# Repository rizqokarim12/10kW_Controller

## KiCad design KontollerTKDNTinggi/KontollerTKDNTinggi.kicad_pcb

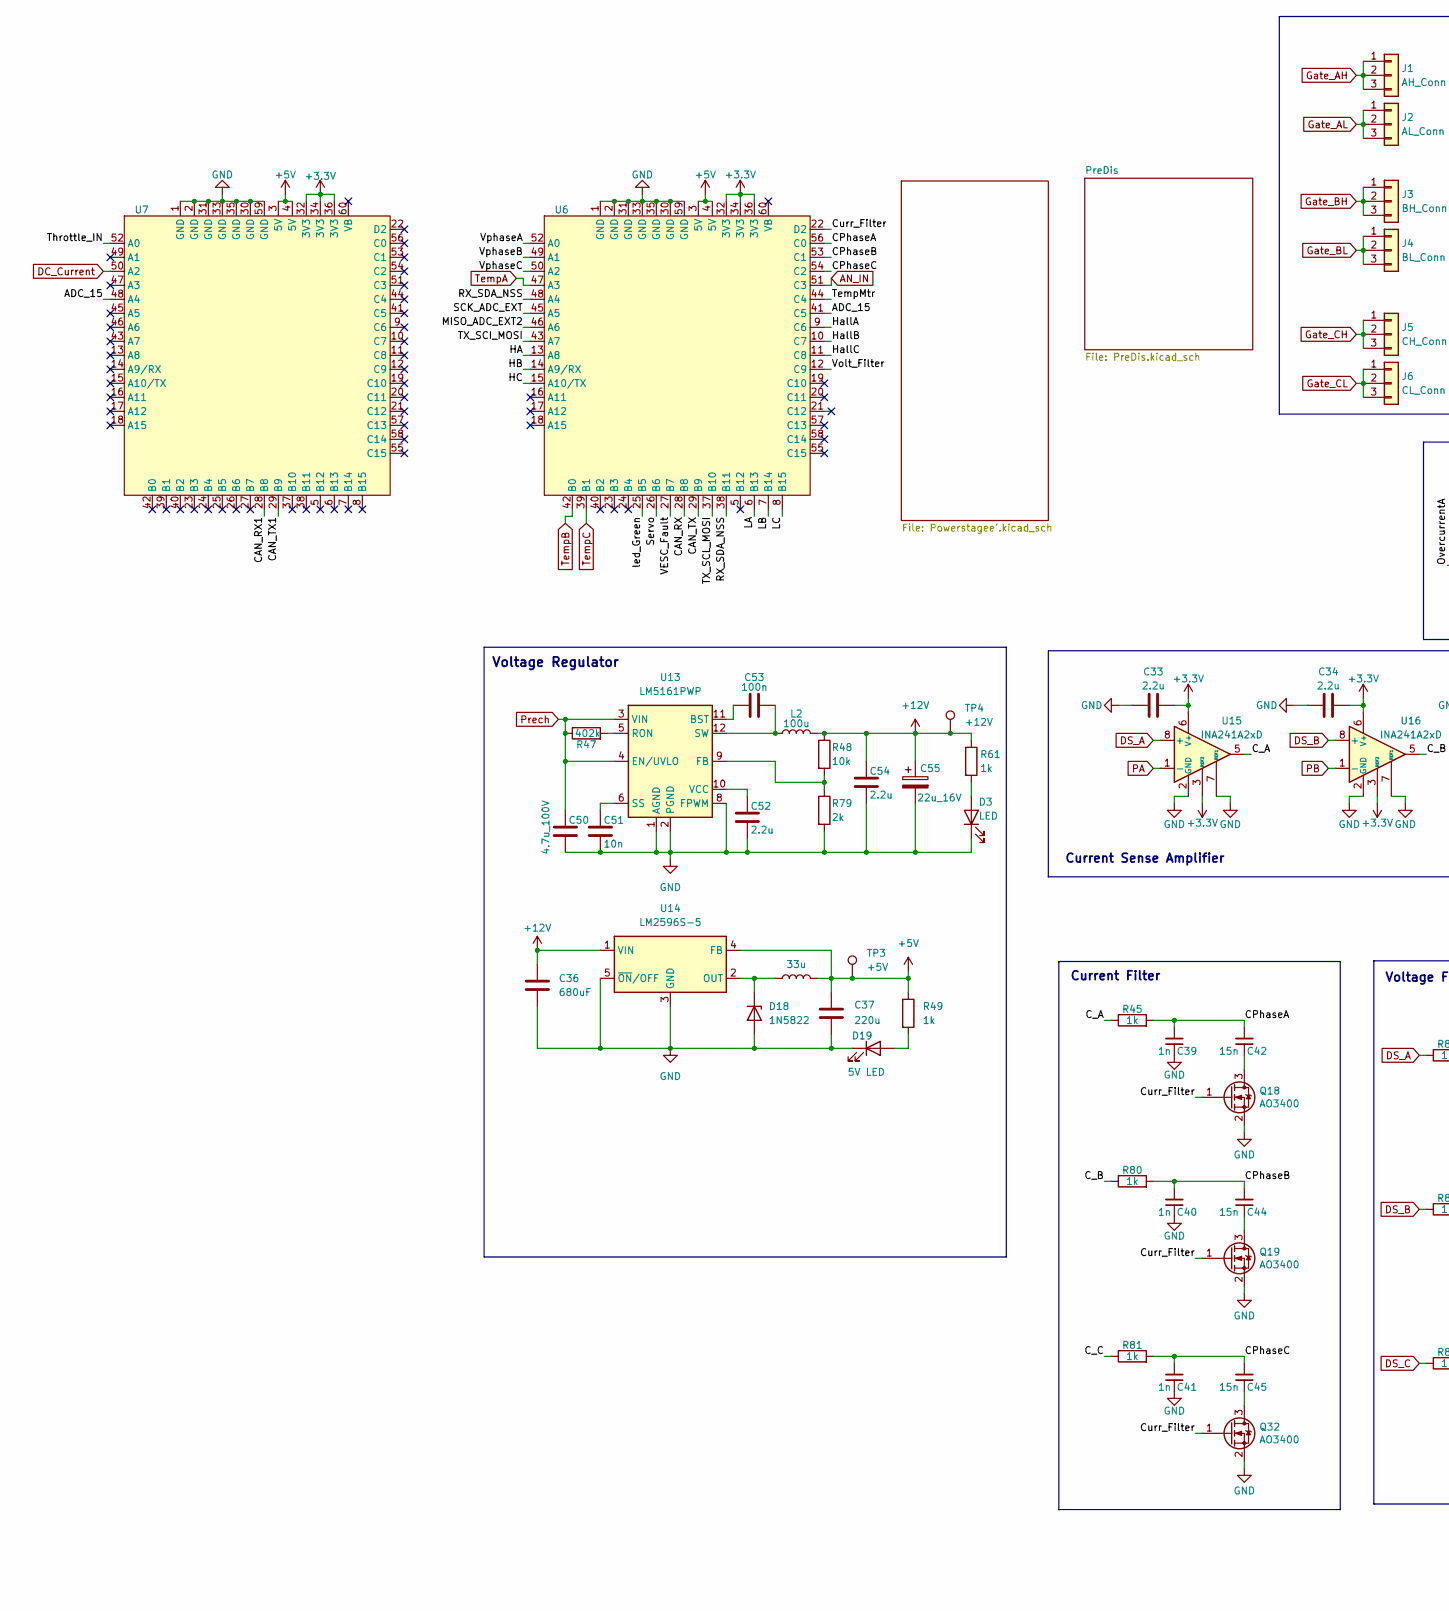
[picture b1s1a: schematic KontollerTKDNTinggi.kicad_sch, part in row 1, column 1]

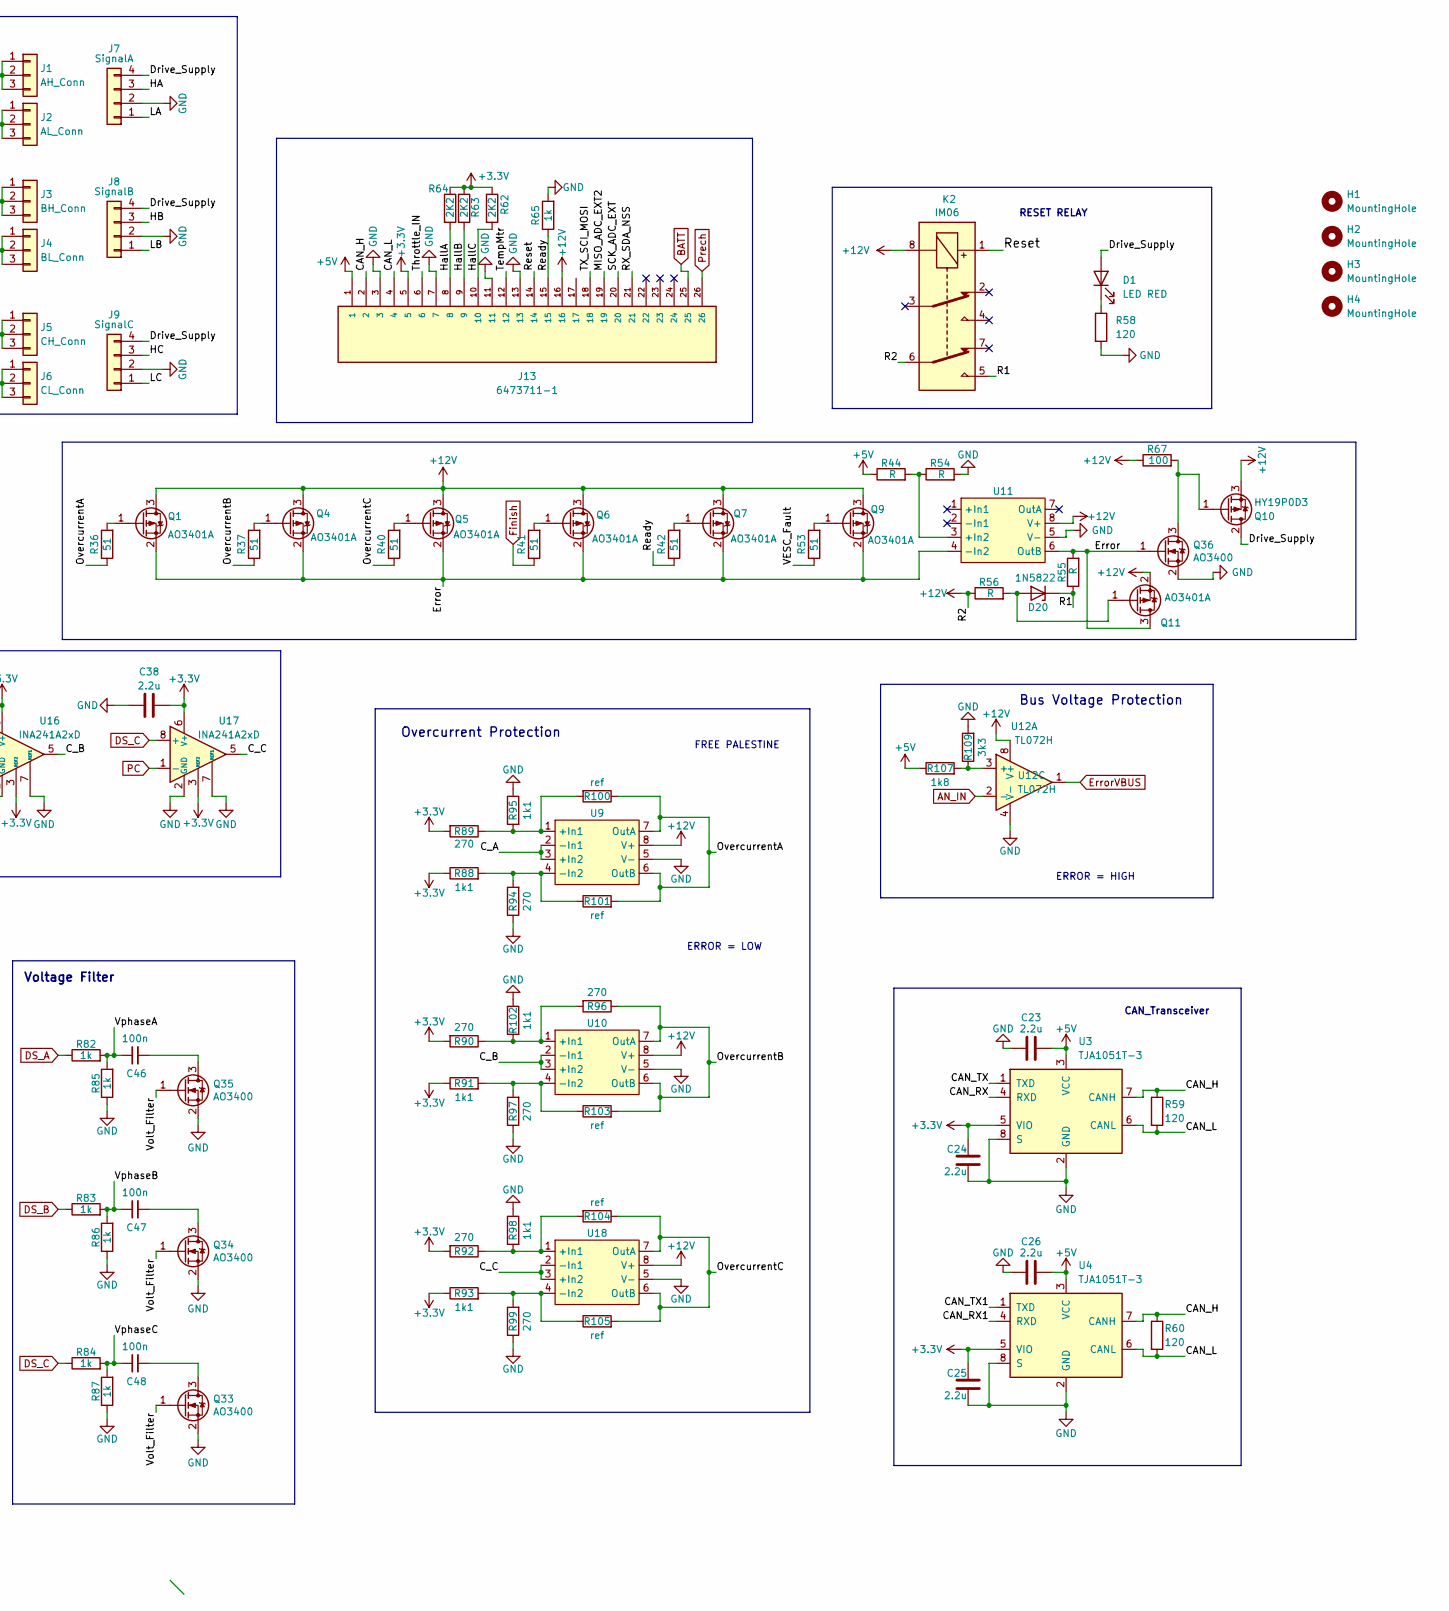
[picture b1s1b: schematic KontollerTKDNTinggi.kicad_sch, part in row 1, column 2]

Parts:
C23, C24, C25, C26, C33, C34, C38, C52, C54: 2.2u; C_0805_2012Metric_Pad1.18x1.45mm_HandSolder
C36: 680uF; CP_Elec_10x10
C37: 220u; C_Elec_6.3x5.4
C39, C40, C41: 1n; C_0805_2012Metric_Pad1.18x1.45mm_HandSolder
C42, C44, C45: 15n; C_0805_2012Metric_Pad1.18x1.45mm_HandSolder
C46, C47, C48, C53: 100n; C_0805_2012Metric_Pad1.18x1.45mm_HandSolder
C50: 4.7u_100V; CP_Elec_6.3x5.2
C51: 10n; C_0805_2012Metric_Pad1.18x1.45mm_HandSolder
C55: 22u_16V; CP_Elec_5x5.4
D1: LED RED; LED_0805_2012Metric_Pad1.15x1.40mm_HandSolder
D3: LED; LED_0805_2012Metric_Pad1.15x1.40mm_HandSolder
D18, D20: 1N5822; D_SMA_Handsoldering
D19: 5V LED; LED_0805_2012Metric_Pad1.15x1.40mm_HandSolder
H1, H2, H3, H4: MountingHole; MountingHole_3mm_Pad_Via
J1: AH_Conn; PinSocket_1x03_P2.54mm_Vertical_SMD_Pin1Left
J2: AL_Conn; PinSocket_1x03_P2.54mm_Vertical_SMD_Pin1Left
J3: BH_Conn; PinSocket_1x03_P2.54mm_Vertical_SMD_Pin1Left
J4: BL_Conn; PinSocket_1x03_P2.54mm_Vertical_SMD_Pin1Left
J5: CH_Conn; PinSocket_1x03_P2.54mm_Vertical_SMD_Pin1Left
J6: CL_Conn; PinSocket_1x03_P2.54mm_Vertical_SMD_Pin1Left
J7: SignalA; PinSocket_1x04_P2.54mm_Vertical_SMD_Pin1Left
J8: SignalB; PinSocket_1x04_P2.54mm_Vertical_SMD_Pin1Left
J9: SignalC; PinSocket_1x04_P2.54mm_Vertical_SMD_Pin1Left
J13: 6473711-1; TE_6473711-1; PART_REV A
K2: IM06; IM06D
L2: 100u; INDM1250X1250X600
L5: 33u; L_10.4x10.4_H4.8
Q1, Q4, Q5, Q6, Q7, Q9, Q11: AO3401A; SOT-23_Handsoldering
Q10: HY19P0D3; TO-252-2
Q18, Q19, Q32, Q33, Q34, Q35, Q36: AO3400; SOT-23_Handsoldering
R36, R37, R40, R41, R42, R53: 51; R_0805_2012Metric_Pad1.20x1.40mm_HandSolder
R44, R54, R55, R56: R; R_0805_2012Metric_Pad1.20x1.40mm_HandSolder
R45, R49, R61, R65, R80, R81, R82, R83, R84, R85, R86, R87: 1k; R_0805_2012Metric_Pad1.20x1.40mm_HandSolder
R47: 402k; R_0805_2012Metric_Pad1.20x1.40mm_HandSolder
R48: 10k; R_0805_2012Metric_Pad1.20x1.40mm_HandSolder
R58, R59, R60: 120; R_0805_2012Metric_Pad1.20x1.40mm_HandSolder
R62, R63, R64: 2K2; R_0805_2012Metric_Pad1.20x1.40mm_HandSolder
R67: 100; R_0805_2012Metric_Pad1.20x1.40mm_HandSolder
R79: 2k; R_0805_2012Metric_Pad1.20x1.40mm_HandSolder
R88, R91, R93, R95, R98, R102: 1k1; R_0805_2012Metric_Pad1.20x1.40mm_HandSolder
R89, R90, R92, R94, R96, R97, R99: 270; R_0805_2012Metric_Pad1.20x1.40mm_HandSolder
R100, R101, R103, R104, R105: ref; R_0805_2012Metric_Pad1.20x1.40mm_HandSolder
R107: 1k8; R_0805_2012Metric_Pad1.20x1.40mm_HandSolder
R109: 3k3; R_0805_2012Metric_Pad1.20x1.40mm_HandSolder
TP3: +5V; TestPoint_Pad_2.0x2.0mm
TP4: +12V; TestPoint_Pad_2.0x2.0mm
U3, U4: TJA1051T-3; SOIC-8_3.9x4.9mm_P1.27mm
U6, U7: STM32F405Weact
U9, U10, U11, U18: SOIC-8_3.9x4.9mm_P1.27mm
U12: TL072H; SOIC-8_3.9x4.9mm_P1.27mm
U13: LM5161PWP; HTSSOP-14-1EP_4.4x5mm_P0.65mm_EP3.4x5mm_Mask3x3.1mm
U14: LM2596S-5; TO-263-5_TabPin3
U15, U16, U17: INA241A2xD; SOIC-8_3.9x4.9mm_P1.27mm

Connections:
+12V: C36.1, C54.1, C55.1, J13.16, K2.6, K2.8, L2.2, Q1.3 (D), Q4.3 (D), Q5.3 (D), Q6.3 (D), Q7.3 (D), Q9.3 (D), Q10.3 (S), Q11.2 (S), R48.1, R56.1, R61.1, R67.1, TP4.1, U9.8 (V+), U10.8 (V+), U11.8 (V+), U12.8 (V+), U14.1 (VIN), U18.8 (V+); also elsewhere on the board
/ADC_15: U6.41 (C5), U7.48 (A4)
/CAN_H: J13.2, R59.1, R60.1, U3.7 (CANH), U4.7 (CANH)
/CAN_L: J13.4, R59.2, R60.2, U3.6 (CANL), U4.6 (CANL)
/CAN_RX: U3.4 (RXD), U6.28 (B8)
/CAN_RX1: U4.4 (RXD), U7.28 (B8)
/CAN_TX: U3.1 (TXD), U6.29 (B9)
/CAN_TX1: U4.1 (TXD), U7.29 (B9)
/CPhaseA: C39.2, C42.2, R45.2, U6.56 (C0)
/CPhaseB: C40.2, C44.2, R80.2, U6.53 (C1)
/CPhaseC: C41.2, C45.2, R81.2, U6.54 (C2)
/C_A: R45.1, U9.2 (-In1), U9.3 (+In2), U15.5
/C_B: R80.1, U10.2 (-In1), U10.3 (+In2), U16.5
/C_C: R81.1, U17.5, U18.2 (-In1), U18.3 (+In2)
/Curr_Filter: Q18.1 (G), Q19.1 (G), Q32.1 (G), U6.22 (D2)
/Drive_Supply: D1.2 (A), J7.4, J8.4, J9.4, Q10.2 (D)
/HA: J7.3, U6.13 (A8)
/HB: J8.3, U6.14 (A9/RX)
/HC: J9.3, U6.15 (A10/TX)
/HallA: J13.8, R64.2, U6.9 (C6)
/HallB: J13.9, R63.2, U6.10 (C7)
/HallC: J13.10, R62.2, U6.11 (C8)
/LA: J7.1, U6.6 (B13)
/LB: J8.1, U6.7 (B14)
/LC: J9.1, U6.8 (B15)
/MISO_ADC_EXT2: J13.19, U6.46 (A6)
/OvercurrentA: R36.1, R100.1, R101.2, U9.6 (OutB), U9.7 (OutA)
/OvercurrentB: R37.1, R96.1, R103.2, U10.6 (OutB), U10.7 (OutA)
/OvercurrentC: R40.1, R104.1, R105.2, U18.6 (OutB), U18.7 (OutA)
/RX_SDA_NSS: J13.21, U6.38 (B11), U6.48 (A4)
/Ready: J13.15, R42.1, R65.1
/Reset: J13.14, K2.1
/SCK_ADC_EXT: J13.20, U6.45 (A5)
/Servo: U6.26 (B6)
/TX_SCI_MOSI: J13.18, U6.43 (A7)
/TX_SCL_MOSI: U6.37 (B10)
/TempMtr: J13.12, U6.44 (C4)
/Throttle_IN: J13.6, U7.52 (A0)
/VESC_Fault: R53.1, U6.27 (B7)
/Volt_Filter: Q33.1 (G), Q34.1 (G), Q35.1 (G), U6.12 (C9)
/VphaseA: C46.1, R82.2, R85.2, U6.52 (A0)
/VphaseB: C47.1, R83.2, R86.2, U6.49 (A1)
/VphaseC: C48.1, R84.2, R87.2, U6.50 (A2)
/led_Green: U6.25 (B5)
AN_IN: U6.51 (C3), U12.2 (-); also elsewhere on the board
DC_Current: U7.50 (A2); also elsewhere on the board
DS_A: R82.1, U15.8 (+); also elsewhere on the board
DS_B: R83.1, U16.8 (+); also elsewhere on the board
DS_C: R84.1, U17.8 (+); also elsewhere on the board
ErrorVBUS: U12.1; also elsewhere on the board
Finish: R41.1; also elsewhere on the board
GND: C23.1, C24.1, C25.1, C26.1, C33.1, C34.1, C36.2, C37.2, C38.1, C39.1, C40.1, C41.1, C50.2, C51.2, C52.2, C54.2, C55.2, D3.1 (K), D18.2 (A), D19.1 (K), J7.2, J8.2, J9.2, J13.3, J13.7, J13.11, J13.13, Q18.2 (S), Q19.2 (S), Q32.2 (S), Q33.2 (S), Q34.2 (S), Q35.2 (S), Q36.2 (S), R54.2, R58.2, R65.2, R79.2, R85.1, R86.1, R87.1, R94.1, R95.1, R97.1, R98.1, R99.1, R102.1, R109.2, U3.2 (GND), U3.8 (S), U4.2 (GND), U4.8 (S), U6.1 (GND), U6.2 (GND), U6.30 (GND), U6.31 (GND), U6.33 (GND), U6.35 (GND), U6.59 (GND), U7.1 (GND), U7.2 (GND), U7.30 (GND), U7.31 (GND), U7.33 (GND), U7.35 (GND), U7.59 (GND), U9.5 (V-), U10.5 (V-), U11.5 (V-), U12.4 (V-), U13.1 (AGND), U13.2 (PGND), U13.8 (FPWM), U13.15 (AGND), U14.3 (GND), U14.5 (~ON/OFF), U15.2 (GND), U15.4 (GND), U15.7 (REF1), U16.2 (GND), U16.4 (GND), U16.7 (REF1), U17.2 (GND), U17.4 (GND), U17.7 (REF1), U18.5 (V-); also elsewhere on the board
Gate_AH: J1.1, J1.2, J1.3; also elsewhere on the board
Gate_AL: J2.1, J2.2, J2.3; also elsewhere on the board
Gate_BH: J3.1, J3.2, J3.3; also elsewhere on the board
Gate_BL: J4.1, J4.2, J4.3; also elsewhere on the board
Gate_CH: J5.1, J5.2, J5.3; also elsewhere on the board
Gate_CL: J6.1, J6.2, J6.3; also elsewhere on the board
unnamed: C53.1, L2.1, U13.12 (SW), U13.13 (SW)
unnamed: D1.1 (K), R58.1
unnamed: D3.2 (A), R61.2
unnamed: D18.1 (K), L5.1, U14.2 (OUT)
unnamed: D19.2 (A), R49.2
unnamed: D20.2 (A), Q11.1 (G), R56.2
unnamed: Q1.1 (G), R36.2
unnamed: Q4.1 (G), R37.2
unnamed: Q5.1 (G), R40.2
unnamed: Q6.1 (G), R41.2
unnamed: Q7.1 (G), R42.2
unnamed: Q9.1 (G), R53.2
unnamed: C42.1, Q18.3 (D)
unnamed: C44.1, Q19.3 (D)
unnamed: C45.1, Q32.3 (D)
unnamed: C48.2, Q33.3 (D)
unnamed: C47.2, Q34.3 (D)
unnamed: C46.2, Q35.3 (D)
unnamed: R89.1, R95.2, R100.2, U9.1 (+In1)
unnamed: R88.2, R94.2, R101.1, U9.4 (-In2)
unnamed: R90.1, R96.2, R102.2, U10.1 (+In1)
unnamed: R91.2, R97.2, R103.1, U10.4 (-In2)
unnamed: R44.2, R54.1, U11.3 (+In2)
unnamed: R107.2, R109.1, U12.3 (+)
unnamed: C53.2, U13.11 (BST)
unnamed: R48.2, R79.1, U13.9 (FB)
unnamed: R47.2, U13.5 (RON)
unnamed: C51.1, U13.6 (SS)
unnamed: C52.1, U13.10 (VCC)
unnamed: R92.1, R98.2, R104.2, U18.1 (+In1)
unnamed: R93.2, R99.2, R105.1, U18.4 (-In2)
PA: U15.1 (-); also elsewhere on the board
PB: U16.1 (-); also elsewhere on the board
PC: U17.1 (-); also elsewhere on the board
Prech: C50.1, J13.26, R47.1, U13.3 (VIN), U13.4 (EN/UVLO); also elsewhere on the board
TempA: U6.47 (A3); also elsewhere on the board
TempB: U6.42 (B0); also elsewhere on the board
TempC: U6.39 (B1); also elsewhere on the board

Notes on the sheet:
Voltage Regulator
CAN_Transceiver
Overcurrent Protection
RESET RELAY
Current Filter
Current Sense Amplifier
Bus Voltage Protection
Voltage Filter
ERROR = LOW
ERROR = HIGH
FREE PALESTINE

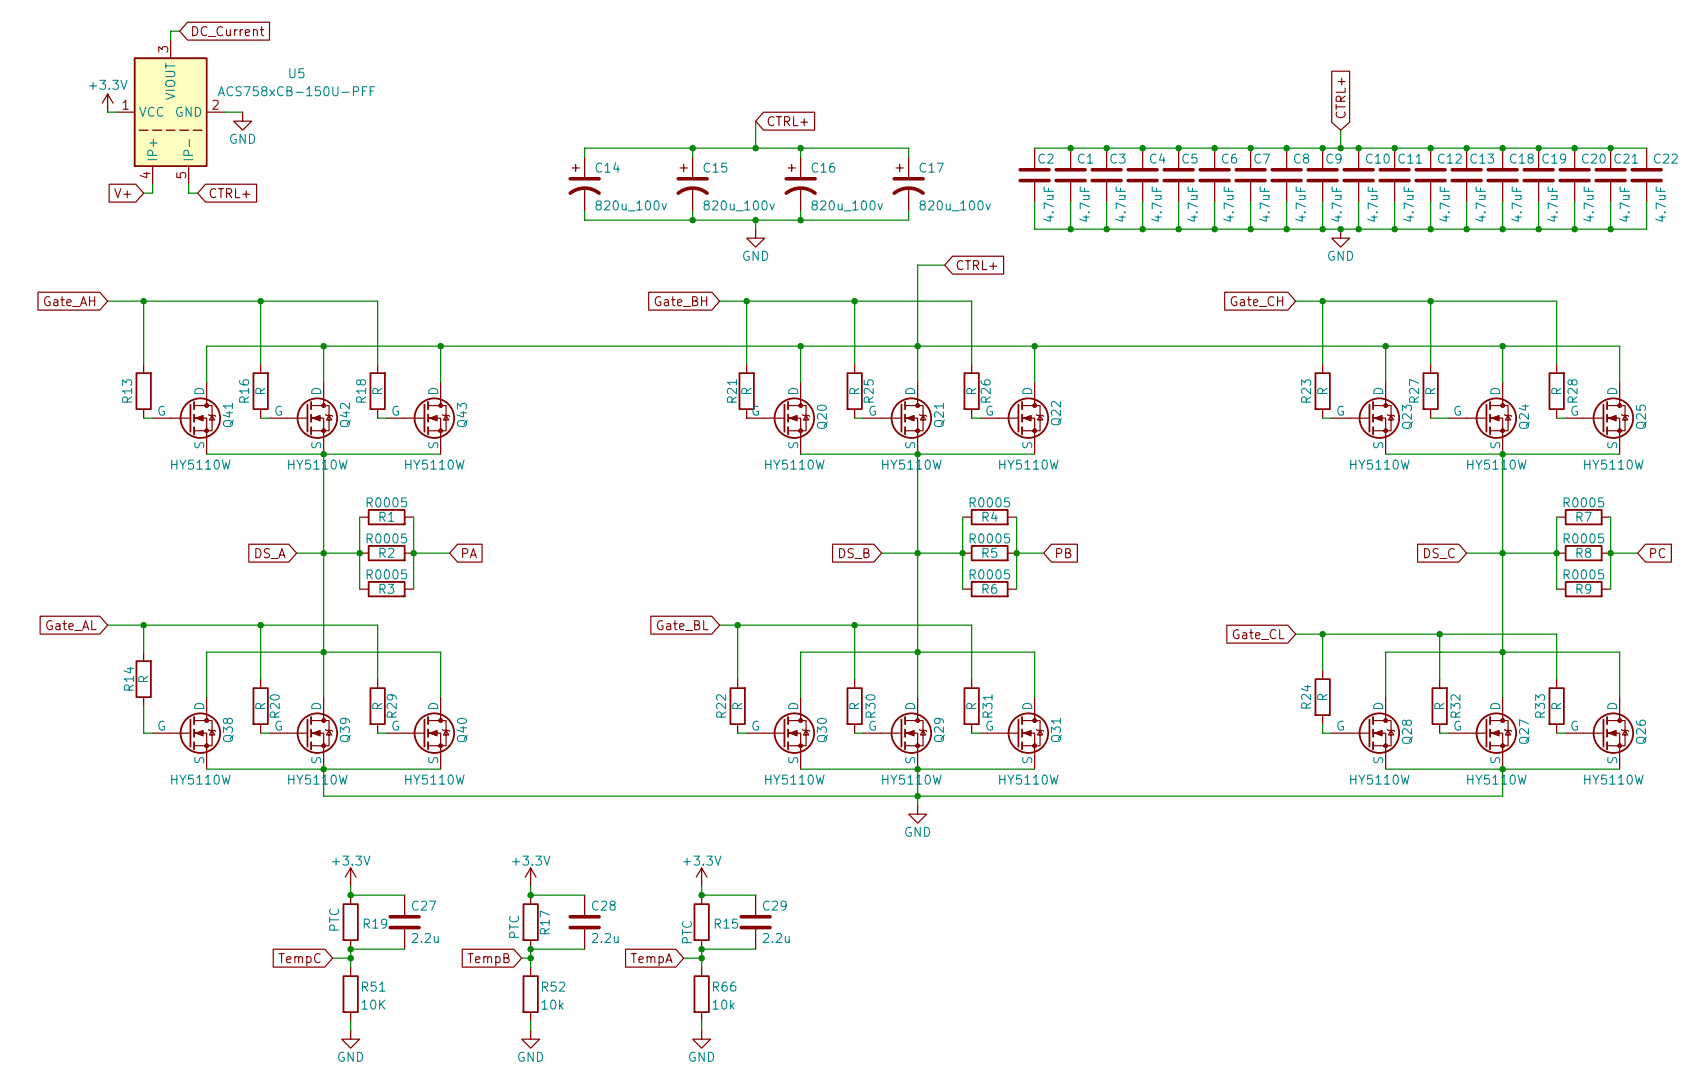
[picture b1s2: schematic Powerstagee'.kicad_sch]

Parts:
C1, C2, C3, C4, C5, C6, C7, C8, C9, C10, C11, C12, C13, C18, C19, C20, C21, C22: 4.7uF; C_1206_3216Metric_Pad1.33x1.80mm_HandSolder
C14, C15, C16, C17: 820u_100v; CP_Radial_D18.0mm_P7.50mm
C27, C28, C29: 2.2u; C_0805_2012Metric_Pad1.18x1.45mm_HandSolder
Q20, Q21, Q22, Q23, Q24, Q25, Q26, Q27, Q28, Q29, Q30, Q31, Q38, Q39, Q40, Q41, Q42, Q43: HY5110W; TO-247 Horizontal Tabup
R1, R2, R3, R4, R5, R6, R7, R8, R9: R0005; R_2512_6332Metric_Pad1.40x3.35mm_HandSolder
R13, R14, R16, R18, R20, R21, R22, R23, R24, R25, R26, R27, R28, R29, R30, R31, R32, R33: R; R_0805_2012Metric_Pad1.20x1.40mm_HandSolder
R15, R17, R19: PTC; R_Axial_DIN0204_L3.6mm_D1.6mm_P1.90mm_Vertical
R51: 10K; R_0805_2012Metric_Pad1.20x1.40mm_HandSolder
R52, R66: 10k; R_0805_2012Metric_Pad1.20x1.40mm_HandSolder
U5: ACS758xCB-150U-PFF; Allegro_CB_PFF

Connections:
CTRL+: C1.1, C2.1, C3.1, C4.1, C5.1, C6.1, C7.1, C8.1, C9.1, C10.1, C11.1, C12.1, C13.1, C14.1, C15.1, C16.1, C17.1, C18.1, C19.1, C20.1, C21.1, C22.1, Q20.1 (D), Q21.1 (D), Q22.1 (D), Q23.1 (D), Q24.1 (D), Q25.1 (D), Q41.1 (D), Q42.1 (D), Q43.1 (D), U5.5 (IP-); also elsewhere on the board
DC_Current: U5.3 (VIOUT); also elsewhere on the board
DS_A: Q38.1 (D), Q39.1 (D), Q40.1 (D), Q41.3 (S), Q42.3 (S), Q43.3 (S), R1.1, R2.1, R3.1; also elsewhere on the board
DS_B: Q20.3 (S), Q21.3 (S), Q22.3 (S), Q29.1 (D), Q30.1 (D), Q31.1 (D), R4.1, R5.1, R6.1; also elsewhere on the board
DS_C: Q23.3 (S), Q24.3 (S), Q25.3 (S), Q26.1 (D), Q27.1 (D), Q28.1 (D), R7.1, R8.1, R9.1; also elsewhere on the board
GND: C1.2, C2.2, C3.2, C4.2, C5.2, C6.2, C7.2, C8.2, C9.2, C10.2, C11.2, C12.2, C13.2, C14.2, C15.2, C16.2, C17.2, C18.2, C19.2, C20.2, C21.2, C22.2, Q26.3 (S), Q27.3 (S), Q28.3 (S), Q29.3 (S), Q30.3 (S), Q31.3 (S), Q38.3 (S), Q39.3 (S), Q40.3 (S), R51.2, R52.2, R66.2, U5.2 (GND); also elsewhere on the board
Gate_AH: R13.2, R16.2, R18.2; also elsewhere on the board
Gate_AL: R14.2, R20.1, R29.1; also elsewhere on the board
Gate_BH: R21.2, R25.1, R26.1; also elsewhere on the board
Gate_BL: R22.2, R30.1, R31.1; also elsewhere on the board
Gate_CH: R23.1, R27.1, R28.2; also elsewhere on the board
Gate_CL: R24.1, R32.2, R33.1; also elsewhere on the board
unnamed: Q20.2 (G), R21.1
unnamed: Q21.2 (G), R25.2
unnamed: Q22.2 (G), R26.2
unnamed: Q23.2 (G), R23.2
unnamed: Q24.2 (G), R27.2
unnamed: Q25.2 (G), R28.1
unnamed: Q26.2 (G), R33.2
unnamed: Q27.2 (G), R32.1
unnamed: Q28.2 (G), R24.2
unnamed: Q29.2 (G), R30.2
unnamed: Q30.2 (G), R22.1
unnamed: Q31.2 (G), R31.2
unnamed: Q38.2 (G), R14.1
unnamed: Q39.2 (G), R20.2
unnamed: Q40.2 (G), R29.2
unnamed: Q41.2 (G), R13.1
unnamed: Q42.2 (G), R16.1
unnamed: Q43.2 (G), R18.1
PA: R1.2, R2.2, R3.2; also elsewhere on the board
PB: R4.2, R5.2, R6.2; also elsewhere on the board
PC: R7.2, R8.2, R9.2; also elsewhere on the board
TempA: C29.2, R15.2, R66.1; also elsewhere on the board
TempB: C28.2, R17.2, R52.1; also elsewhere on the board
TempC: C27.2, R19.2, R51.1; also elsewhere on the board
V+: U5.4 (IP+); also elsewhere on the board

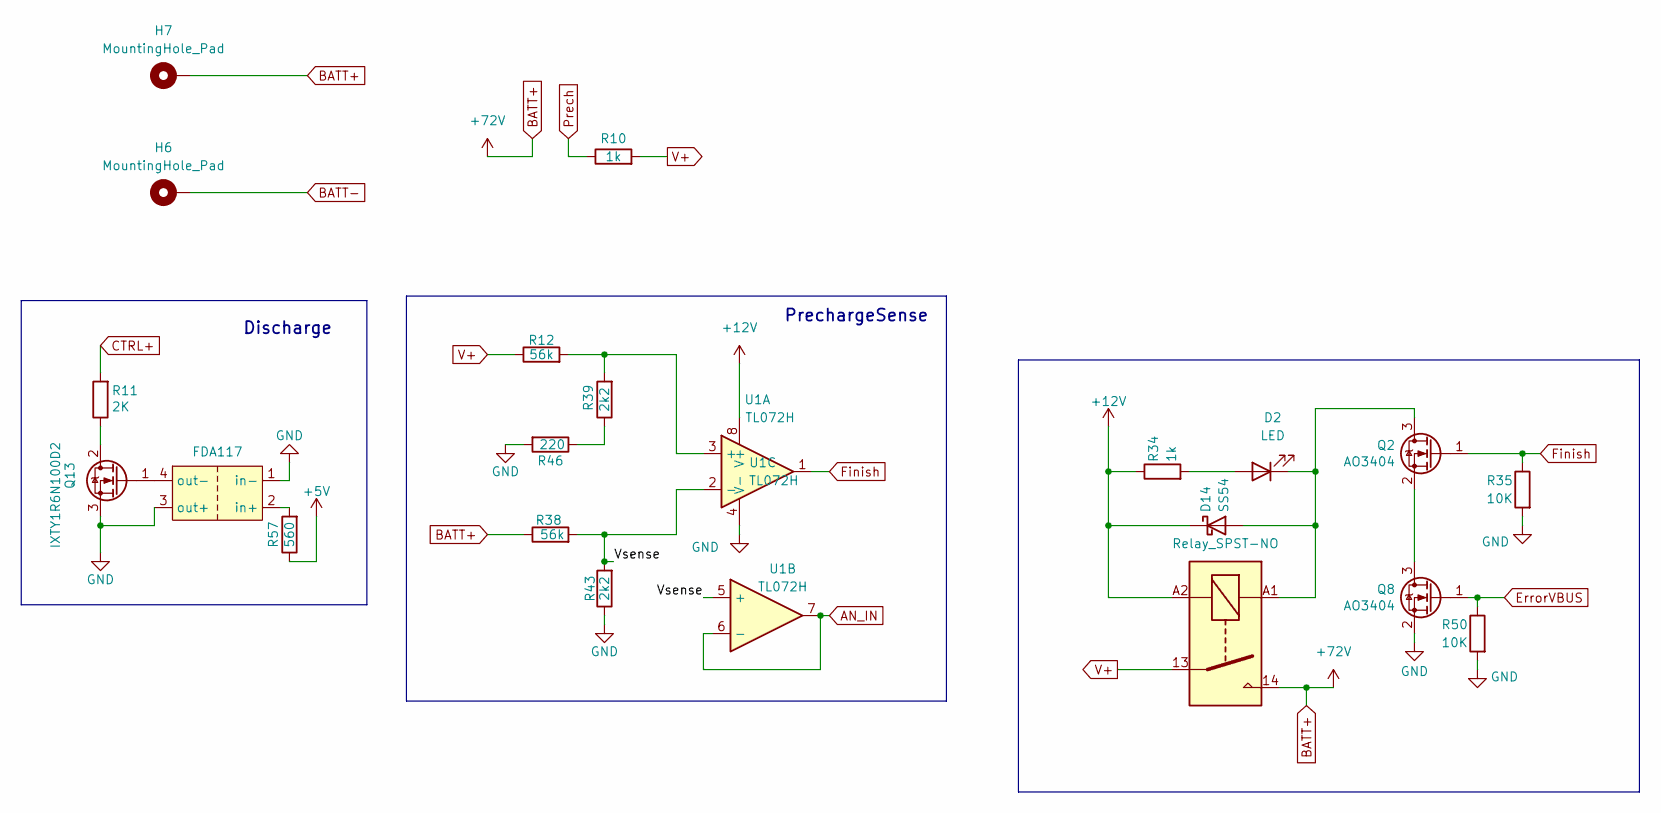
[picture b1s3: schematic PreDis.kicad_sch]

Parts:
D2: LED; LED_0805_2012Metric_Pad1.15x1.40mm_HandSolder
D14: SS54; D_SMA_Handsoldering
FDA117: FDA117
H6, H7: MountingHole_Pad; MountingHole_6.4mm_M6_Pad_Via
K1: Relay_SPST-NO; RELAY100A
Q2, Q8: AO3404; SOT-23_Handsoldering
Q13: IXTY1R6N100D2; TO-252-2
R10: 1k; R_Axial_DIN0918_L18.0mm_D9.0mm_P30.48mm_Horizontal
R11: 2K; R_Axial_DIN0617_L17.0mm_D6.0mm_P20.32mm_Horizontal
R12: 56k; R_0805_2012Metric_Pad1.20x1.40mm_HandSolder
R34: 1k; R_0805_2012Metric_Pad1.20x1.40mm_HandSolder
R35, R50: 10K; R_0805_2012Metric_Pad1.20x1.40mm_HandSolder
R38: 56k; R_1206_3216Metric_Pad1.30x1.75mm_HandSolder
R39, R43: 2k2; R_1206_3216Metric_Pad1.30x1.75mm_HandSolder
R46: 220; R_1206_3216Metric_Pad1.30x1.75mm_HandSolder
R57: 560; R_0805_2012Metric_Pad1.20x1.40mm_HandSolder
U1: TL072H; SOIC-8_3.9x4.9mm_P1.27mm

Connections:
+12V: D14.1 (K), K1.A2, R34.1, U1.8 (V+); also elsewhere on the board
/PreDis/Vsense: R38.2, R43.2, U1.2 (-), U1.5 (+)
AN_IN: U1.6 (-), U1.7; also elsewhere on the board
BATT-: H6.1
CTRL+: R11.2; also elsewhere on the board
ErrorVBUS: Q8.1 (G), R50.1; also elsewhere on the board
Finish: Q2.1 (G), R35.1, U1.1; also elsewhere on the board
GND: FDA117.1 (in-), FDA117.3 (out+), Q8.2 (S), Q13.3 (S), R35.2, R43.1, R46.2, R50.2, U1.4 (V-); also elsewhere on the board
unnamed: D2.2 (A), R34.2
unnamed: D2.1 (K), D14.2 (A), K1.A1, Q2.3 (D)
unnamed: FDA117.2 (in+), R57.2
unnamed: FDA117.4 (out-), Q13.1 (G)
unnamed: Q2.2 (S), Q8.3 (D)
unnamed: Q13.2 (D), R11.1
unnamed: R39.1, R46.1
unnamed: R12.2, R39.2, U1.3 (+)
Prech: R10.1; also elsewhere on the board
V+: K1.13, R10.2, R12.1; also elsewhere on the board

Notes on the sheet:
Discharge
PrechargeSense

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
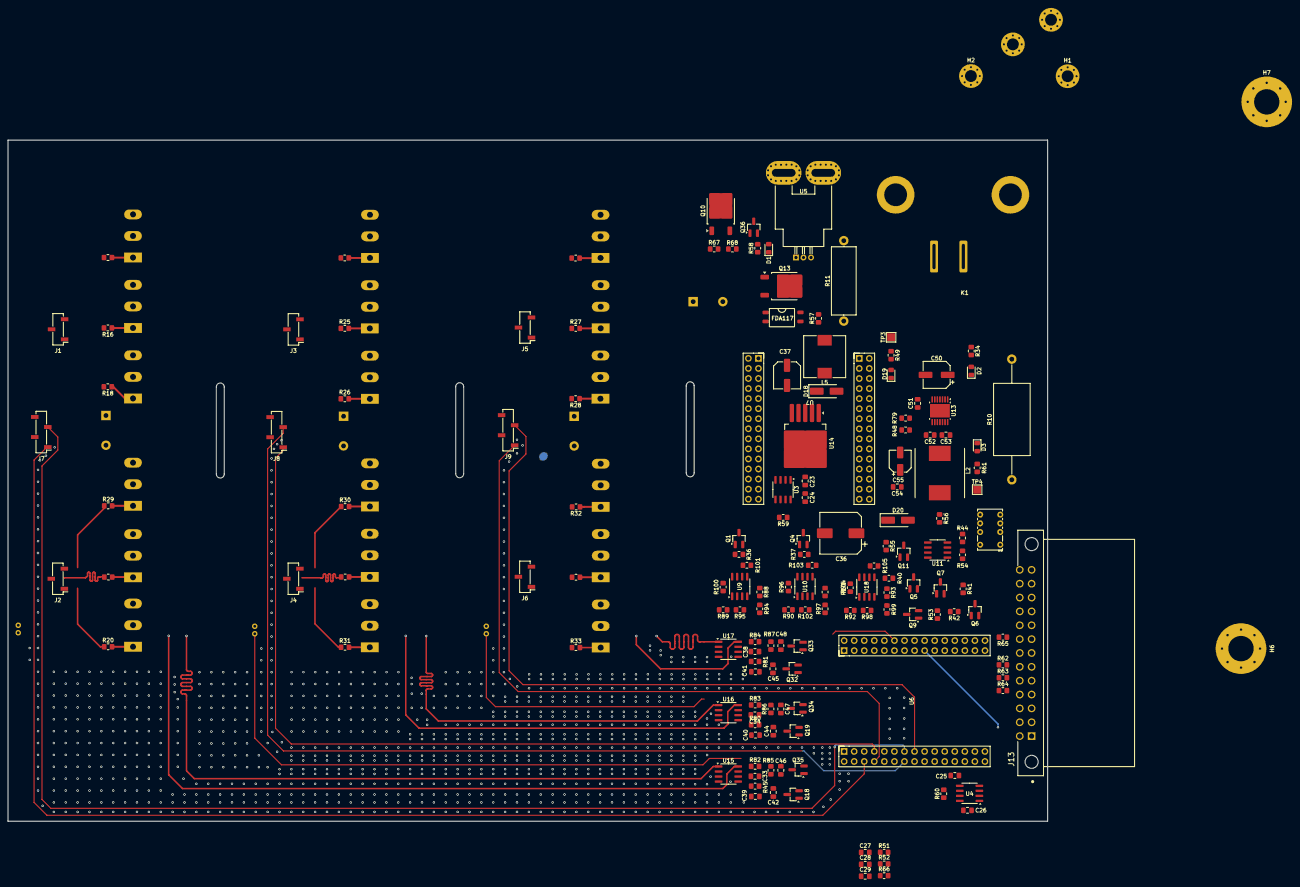
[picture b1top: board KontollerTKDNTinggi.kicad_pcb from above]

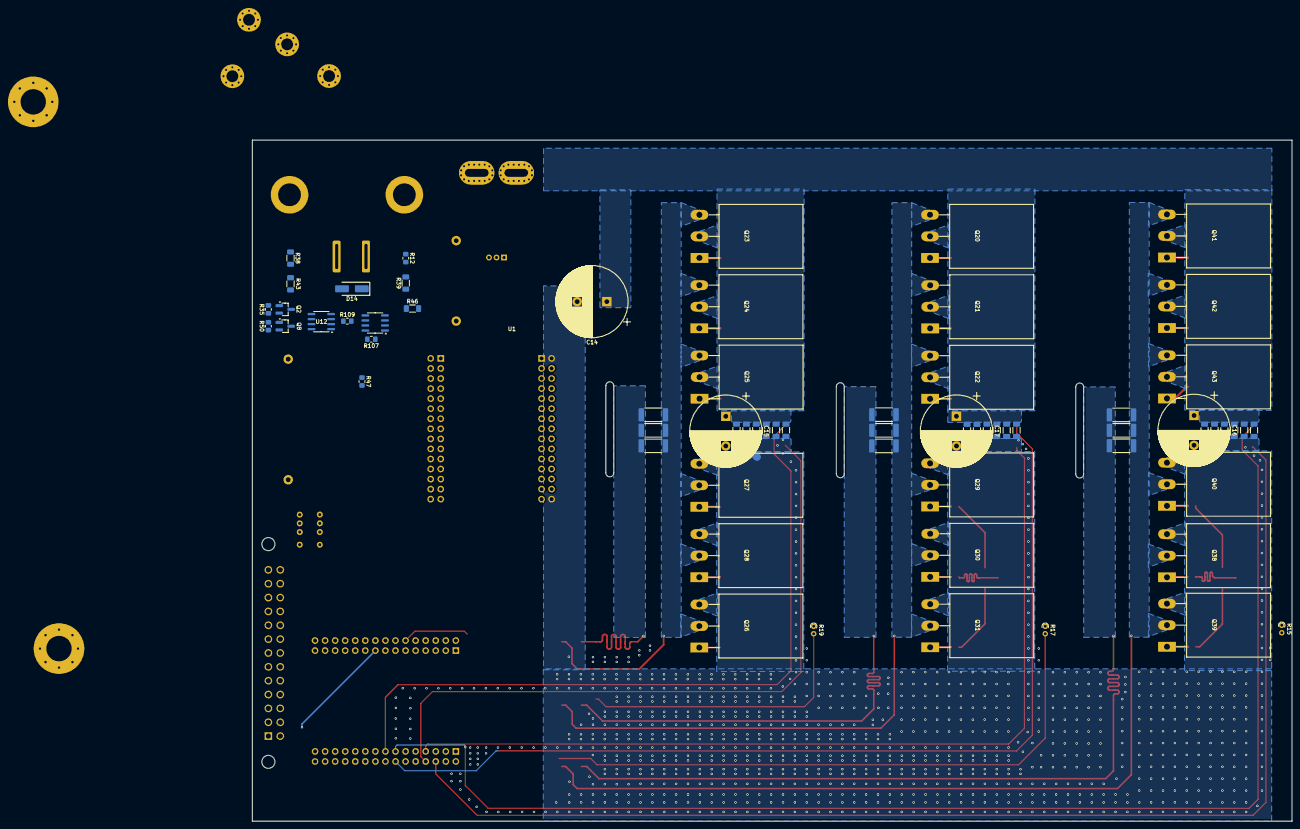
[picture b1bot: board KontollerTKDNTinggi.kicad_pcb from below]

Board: 4 copper layers, 262.6 x 172.1 mm, 228 parts (67 on the bottom side), 130 nets.

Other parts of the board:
R68: 1k; R_0805_2012Metric_Pad1.20x1.40mm_HandSolder

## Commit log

2025-11-10 ngetesdoang
2025-11-10 real
2025-11-10 imarealnigga
2025-11-10 mynigga
2025-11-10 freePalestine
2025-11-11 11Nov
2025-11-12 ganticonnector
2025-11-13 13Nov
2025-11-18 18November
2025-11-24 nigeria
2025-11-24 24Nov26
2025-12-01 mendekatifix
2025-12-10 10nov
2025-12-10 test
